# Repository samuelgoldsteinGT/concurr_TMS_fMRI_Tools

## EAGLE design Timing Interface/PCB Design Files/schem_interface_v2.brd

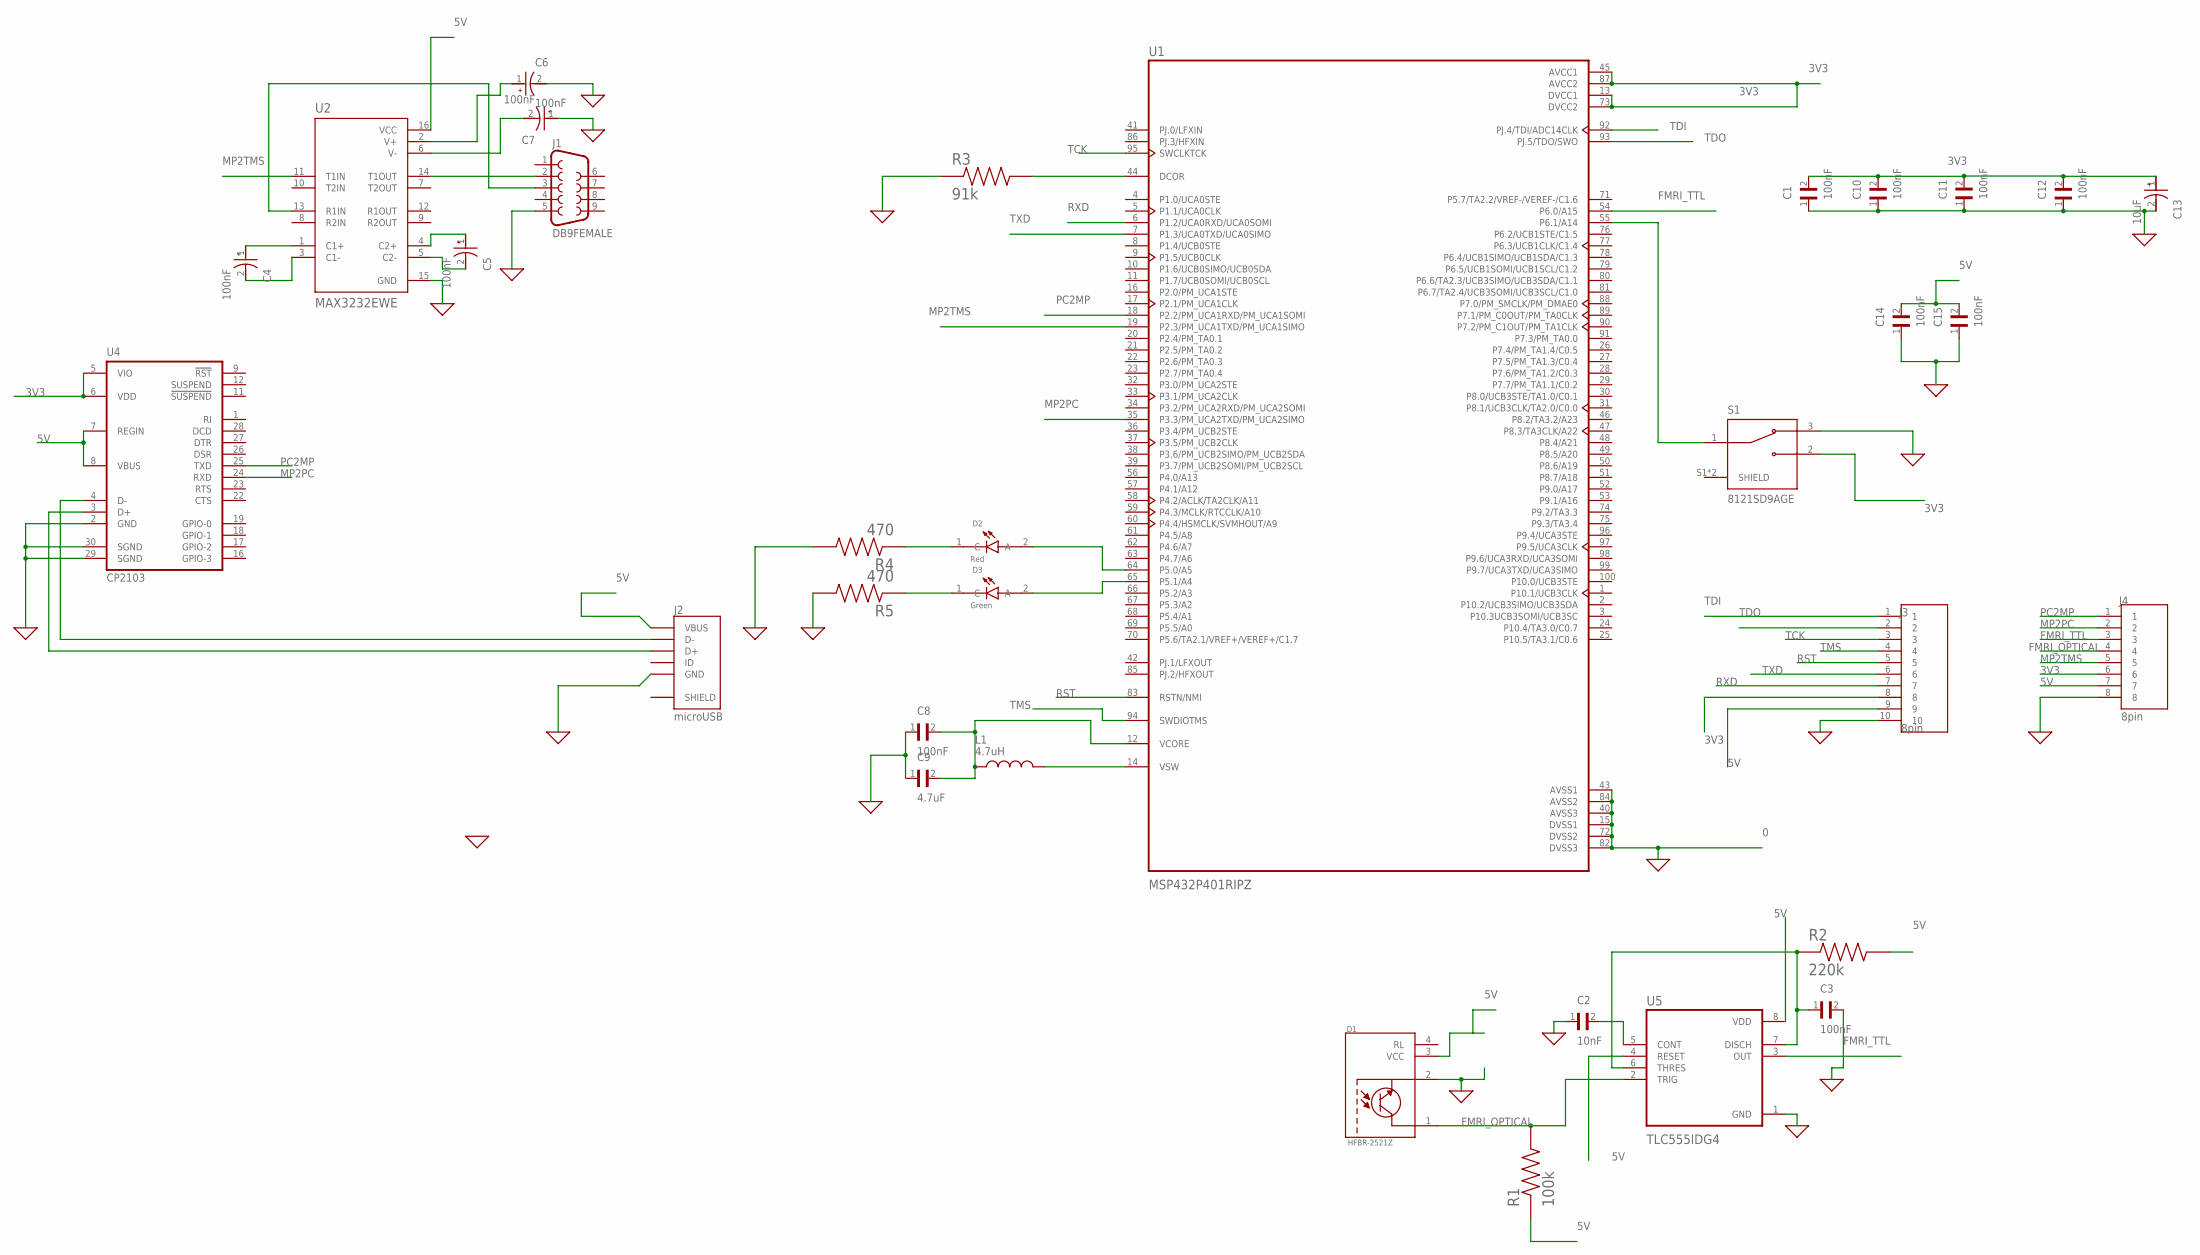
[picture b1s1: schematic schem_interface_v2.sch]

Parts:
C1, C3, C8, C10, C11, C12, C14, C15: 100nF; CAPC3216X178N
C2: 10nF; CAPC3216X178N
C4, C5, C6, C7: 100nF; CAPMP3216X180N
C9: 4.7uF; CAPC3216X178N
C13: 10uF; CAPMP3216X180N
D1: HFBR-2521Z; OPTO_HFBR-2521Z
D2: Red; LEDC3216X110N
D3: Green; LEDC3216X110N
J1: DB9FEMALE; DB9
J2: microUSB; GCT_USB3090-XX-X_REVE
J3: 8pin; TE_4-644456-0
J4: 8pin; TE_5-146282-8
L1: 4.7uH; INDC2012X100N
R1: 100k; RESC6432X70N
R2: 220k; RESC6432X70N
R3: 91k; RESC6432X70N
R4, R5: 470; RESC6432X70N
S1: 8121SD9AGE; SW_8121SD9AGE
U1: MSP432P401RIPZ; QFP50P1600X1600X160-100N
U2: MAX3232EWE; SOIC127P1032X265-16N
U4: CP2103; QFN28
U5: TLC555IDG4; SOIC127P599X175-8N

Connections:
0: C1.1, C2.1, C3.2, C6.2, C7.1, C8.1, C9.1, C10.1, C11.1, C12.1, C13.2, C14.1, C15.1, D1.2 (GROUND), J1.5, J2.5 (GND), J3.10, J4.8, R3.1, R4.2, R5.2, S1.3, U1.15 (DVSS1), U1.40 (AVSS3), U1.43 (AVSS1), U1.72 (DVSS2), U1.82 (DVSS3), U1.84 (AVSS2), U2.15 (GND), U4.2 (GND), U4.29 (SGND), U4.30 (SGND), U5.1 (GND)
3V3: C1.2, C10.2, C11.2, C12.2, C13.1, J3.8, J4.6, S1.2, U1.13 (DVCC1), U1.45 (AVCC1), U1.73 (DVCC2), U1.87 (AVCC2), U4.5 (VIO), U4.6 (VDD)
5V: C14.2, C15.2, D1.3 (VCC), J2.1 (VBUS), J3.9, J4.7, R1.1, R2.2, U2.16 (VCC), U4.7 (REGIN), U4.8 (VBUS), U5.4 (RESET), U5.8 (VDD)
FMRI_OPTICAL: D1.1 (VO), J4.4, R1.2, U5.2 (TRIG)
FMRI_TTL: J4.3, U1.54 (P6.0/A15), U5.3 (OUT)
MP2PC: J4.2, U1.35 (P3.3/PM_UCA2TXD/PM_UCA2SIMO), U4.24 (RXD)
MP2TMS: J4.5, U1.19 (P2.3/PM_UCA1TXD/PM_UCA1SIMO), U2.11 (T1IN)
unnamed: D2.1 (C), R4.1
unnamed: C2.2, U5.5 (CONT)
unnamed: C3.1, R2.1, U5.6 (THRES), U5.7 (DISCH)
unnamed: J1.2, U2.14 (T1OUT)
unnamed: C6.1, U2.2 (V+)
unnamed: J1.3, U2.13 (R1IN)
unnamed: C7.2, U2.6 (V-)
unnamed: R3.2, U1.44 (DCOR)
unnamed: D2.2 (A), U1.64 (P5.0/A5)
unnamed: C5.1, U2.4 (C2+)
unnamed: C5.2, U2.5 (C2-)
unnamed: C4.1, U2.1 (C1+)
unnamed: C4.2, U2.3 (C1-)
unnamed: L1.2, U1.14 (VSW)
unnamed: C8.2, C9.2, L1.1, U1.12 (VCORE)
unnamed: D3.2 (A), U1.65 (P5.1/A4)
unnamed: D3.1 (C), R5.1
unnamed: J2.3 (D+), U4.3 (D+)
unnamed: S1.1, U1.55 (P6.1/A14)
unnamed: J2.2 (D-), U4.4 (D-)
PC2MP: J4.1, U1.18 (P2.2/PM_UCA1RXD/PM_UCA1SOMI), U4.25 (TXD)
RST: J3.5, U1.83 (RSTN/NMI)
RXD: J3.7, U1.6 (P1.2/UCA0RXD/UCA0SOMI)
SHIELD: J2.6 (SHIELD), J2.7 (SHIELD), J2.8 (SHIELD), J2.9 (SHIELD)
TCK: J3.3, U1.95 (SWCLKTCK)
TDI: J3.1, U1.92 (PJ.4/TDI/ADC14CLK)
TDO: J3.2, U1.93 (PJ.5/TDO/SWO)
TMS: J3.4, U1.94 (SWDIOTMS)
TXD: J3.6, U1.7 (P1.3/UCA0TXD/UCA0SIMO)

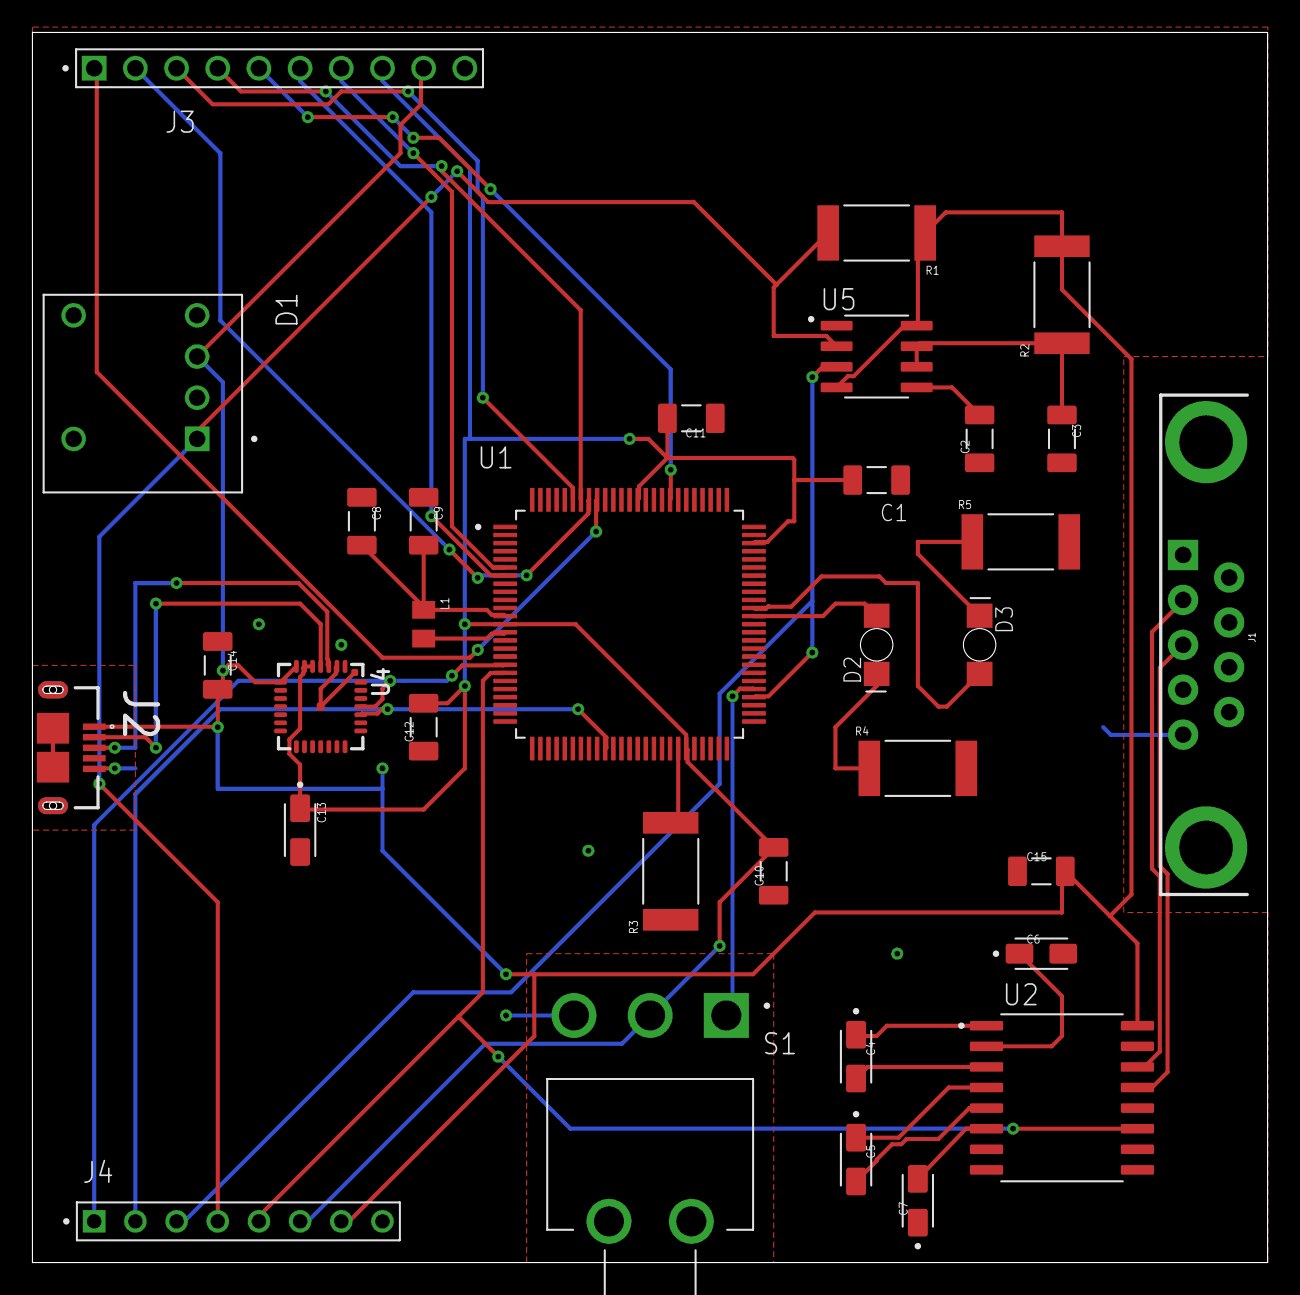
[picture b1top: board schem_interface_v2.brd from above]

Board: 2 copper layers, 76.2 x 75.9 mm, 33 parts (0 on the bottom side), 36 nets.

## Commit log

2021-11-10 first
2022-02-01 tms_localization
2022-02-01 TMS localization code
